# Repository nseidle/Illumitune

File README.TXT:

Illumitune is a exhibit at a kid's museum that has 8 infrared channels. When a channel is broken, a light turns on and a tone is played.

More information can be found at: http://www.sparkfun.com/tutorials/282

This repository contains all the firmware and design files for the various parts of the electronics. It also contains the logs from various dates. These logs show the usage information and are used for debugging and use trends.

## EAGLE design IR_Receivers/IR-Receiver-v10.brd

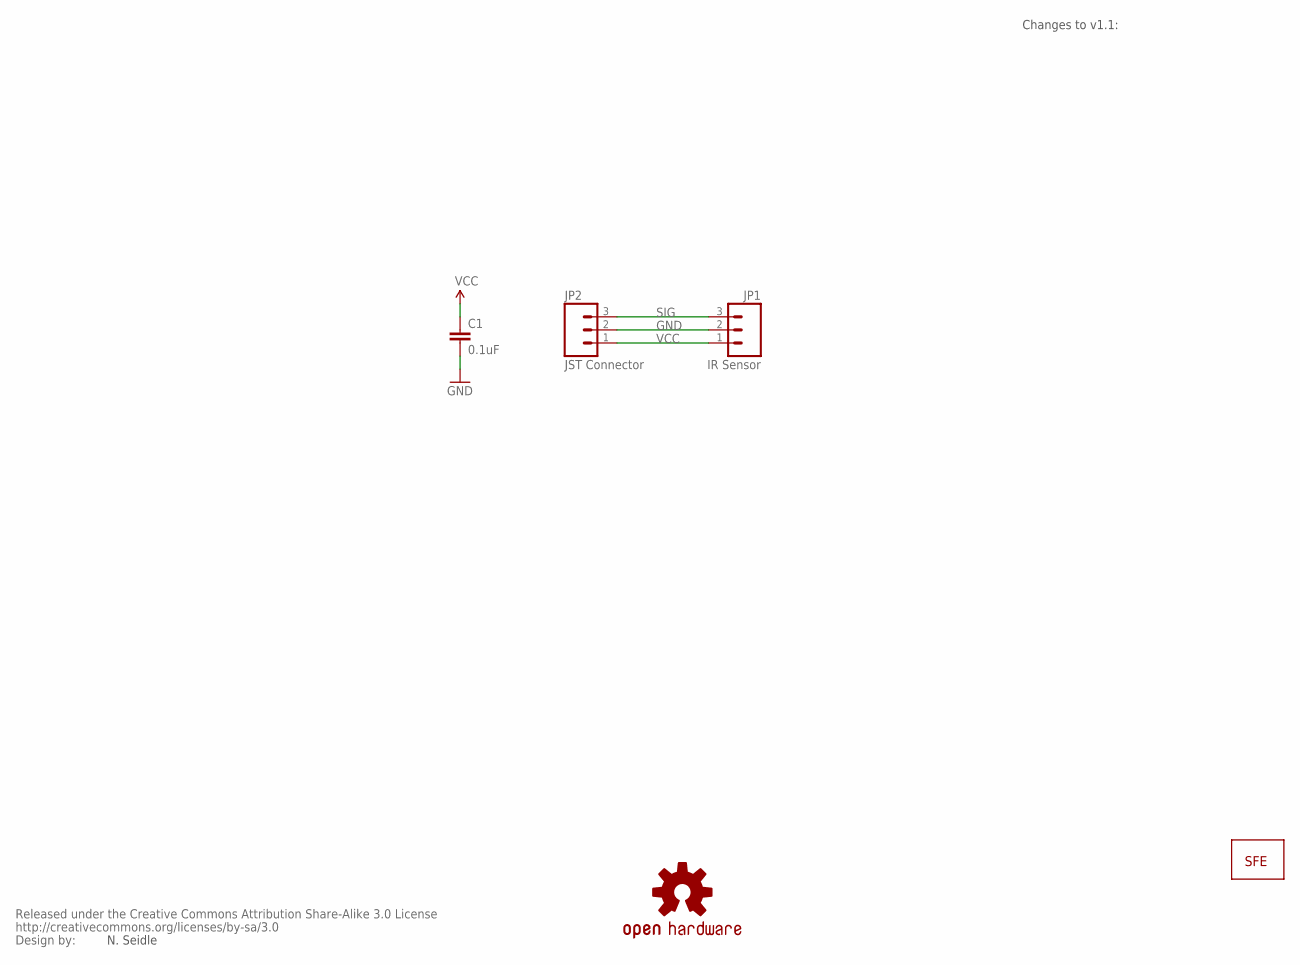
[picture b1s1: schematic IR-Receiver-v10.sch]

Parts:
C1: 0.1uF; CAP-PTH-SMALL2
JP1: IR Sensor; 1X03
JP2: JST Connector; JST-3-PTH
U$1: LOGO-SFESK; SFE-LOGO-FLAME
U$2: CREATIVE_COMMONS
U$4: OSHW-LOGOS; OSHW-LOGO-S

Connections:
GND: C1.2, JP1.2, JP2.2
SIG: JP1.3, JP2.3
VCC: C1.1, JP1.1, JP2.1

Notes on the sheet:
N. Seidle
Changes to v1.1:

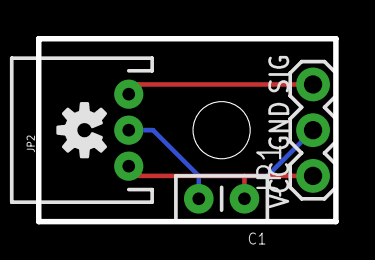
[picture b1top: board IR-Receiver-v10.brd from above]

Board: 2 copper layers, 16.5 x 10.2 mm, 6 parts (1 on the bottom side), 3 nets.

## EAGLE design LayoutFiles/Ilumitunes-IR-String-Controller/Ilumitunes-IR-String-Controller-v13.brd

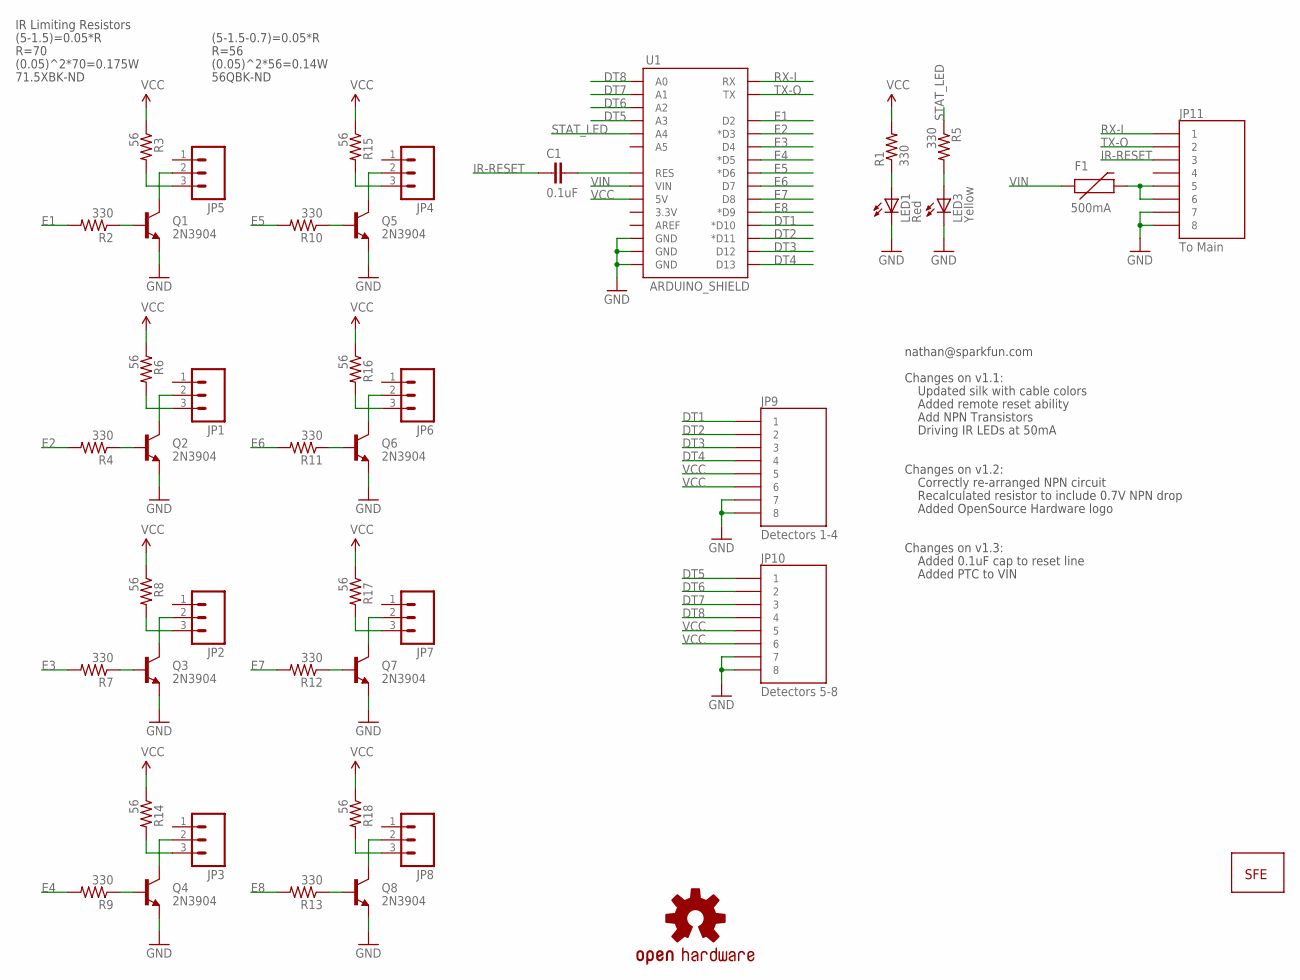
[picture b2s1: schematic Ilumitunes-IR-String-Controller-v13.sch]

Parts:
C1: 0.1uF; CAP-PTH-SMALL2
F1: 500mA; PTC
JP1, JP2, JP3, JP4, JP5, JP6, JP7, JP8: M03JST-PTH-VERT; JST-3-PTH-VERT
JP9: Detectors 1-4; RJ45-8
JP10: Detectors 5-8; RJ45-8
JP11: To Main; RJ45-8
LED1: Red; LED5MM
LED3: Yellow; LED5MM
Q1, Q2, Q3, Q4, Q5, Q6, Q7, Q8: 2N3904; TO-92
R1, R2, R4, R5, R7, R9, R10, R11, R12, R13: 330; AXIAL-0.3
R3, R6, R8, R14, R15, R16, R17, R18: 56; AXIAL-0.3
U1: ARDUINO_SHIELD; DUEMILANOVE_SHIELD_NOHOLES
U$1: LOGO-SFENEW; SFE-NEW-WEBLOGO
U$3: OSHW-LOGOS; OSHW-LOGO-S

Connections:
DT1: JP9.1, U1.D10 (*D10)
DT2: JP9.2, U1.D11 (*D11)
DT3: JP9.3, U1.D12
DT4: JP9.4, U1.D13
DT5: JP10.1, U1.A3
DT6: JP10.2, U1.A2
DT7: JP10.3, U1.A1
DT8: JP10.4, U1.A0
E1: R2.P$2 (2), U1.D2
E2: R4.P$2 (2), U1.D3 (*D3)
E3: R7.P$2 (2), U1.D4
E4: R9.P$2 (2), U1.D5 (*D5)
E5: R10.P$2 (2), U1.D6 (*D6)
E6: R11.P$2 (2), U1.D7
E7: R12.P$2 (2), U1.D8
E8: R13.P$2 (2), U1.D9 (*D9)
GND: JP9.7, JP9.8, JP10.7, JP10.8, JP11.7, JP11.8, LED1.K (C), LED3.K (C), Q1.1 (E), Q2.1 (E), Q3.1 (E), Q4.1 (E), Q5.1 (E), Q6.1 (E), Q7.1 (E), Q8.1 (E), U1.GND@0 (GND), U1.GND@1 (GND), U1.GND@2 (GND)
IR-RESET: C1.1, JP11.3
unnamed: LED1.A, R1.P$1 (1)
unnamed: Q1.2 (B), R2.P$1 (1)
unnamed: JP5.2, Q1.3 (C)
unnamed: LED3.A, R5.P$2 (2)
unnamed: JP5.3, R3.P$2 (2)
unnamed: JP1.2, Q2.3 (C)
unnamed: JP3.2, Q4.3 (C)
unnamed: JP8.2, Q8.3 (C)
unnamed: Q2.2 (B), R4.P$1 (1)
unnamed: JP1.3, R6.P$2 (2)
unnamed: Q3.2 (B), R7.P$1 (1)
unnamed: Q4.2 (B), R9.P$1 (1)
unnamed: Q6.2 (B), R11.P$1 (1)
unnamed: JP4.2, Q5.3 (C)
unnamed: JP6.3, R16.P$2 (2)
unnamed: Q7.2 (B), R12.P$1 (1)
unnamed: JP2.3, R8.P$2 (2)
unnamed: JP3.3, R14.P$2 (2)
unnamed: Q5.2 (B), R10.P$1 (1)
unnamed: C1.2, U1.RES
unnamed: JP4.3, R15.P$2 (2)
unnamed: JP6.2, Q6.3 (C)
unnamed: JP7.3, R17.P$2 (2)
unnamed: Q8.2 (B), R13.P$1 (1)
unnamed: JP7.2, Q7.3 (C)
unnamed: JP8.3, R18.P$2 (2)
unnamed: JP2.2, Q3.3 (C)
unnamed: F1.P$2 (2), JP11.5, JP11.6
RX-I: JP11.1, U1.RX
STAT_LED: R5.P$1 (1), U1.A4
TX-O: JP11.2, U1.TX
VCC: JP9.5, JP9.6, JP10.5, JP10.6, R1.P$2 (2), R3.P$1 (1), R6.P$1 (1), R8.P$1 (1), R14.P$1 (1), R15.P$1 (1), R16.P$1 (1), R17.P$1 (1), R18.P$1 (1), U1.5V
VIN: F1.P$1 (1), U1.VIN

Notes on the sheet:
Changes on v1.1:
Updated silk with cable colors
Added remote reset ability
nathan@sparkfun.com
Add NPN Transistors
(5-1.5)=0.05*R
R=70
(0.05)^2*70=0.175W
71.5XBK-ND
Driving IR LEDs at 50mA
IR Limiting Resistors
(5-1.5-0.7)=0.05*R
R=56
(0.05)^2*56=0.14W
56QBK-ND
Changes on v1.2:
Correctly re-arranged NPN circuit
Recalculated resistor to include 0.7V NPN drop
Added OpenSource Hardware logo
Changes on v1.3:
Added 0.1uF cap to reset line
Added PTC to VIN

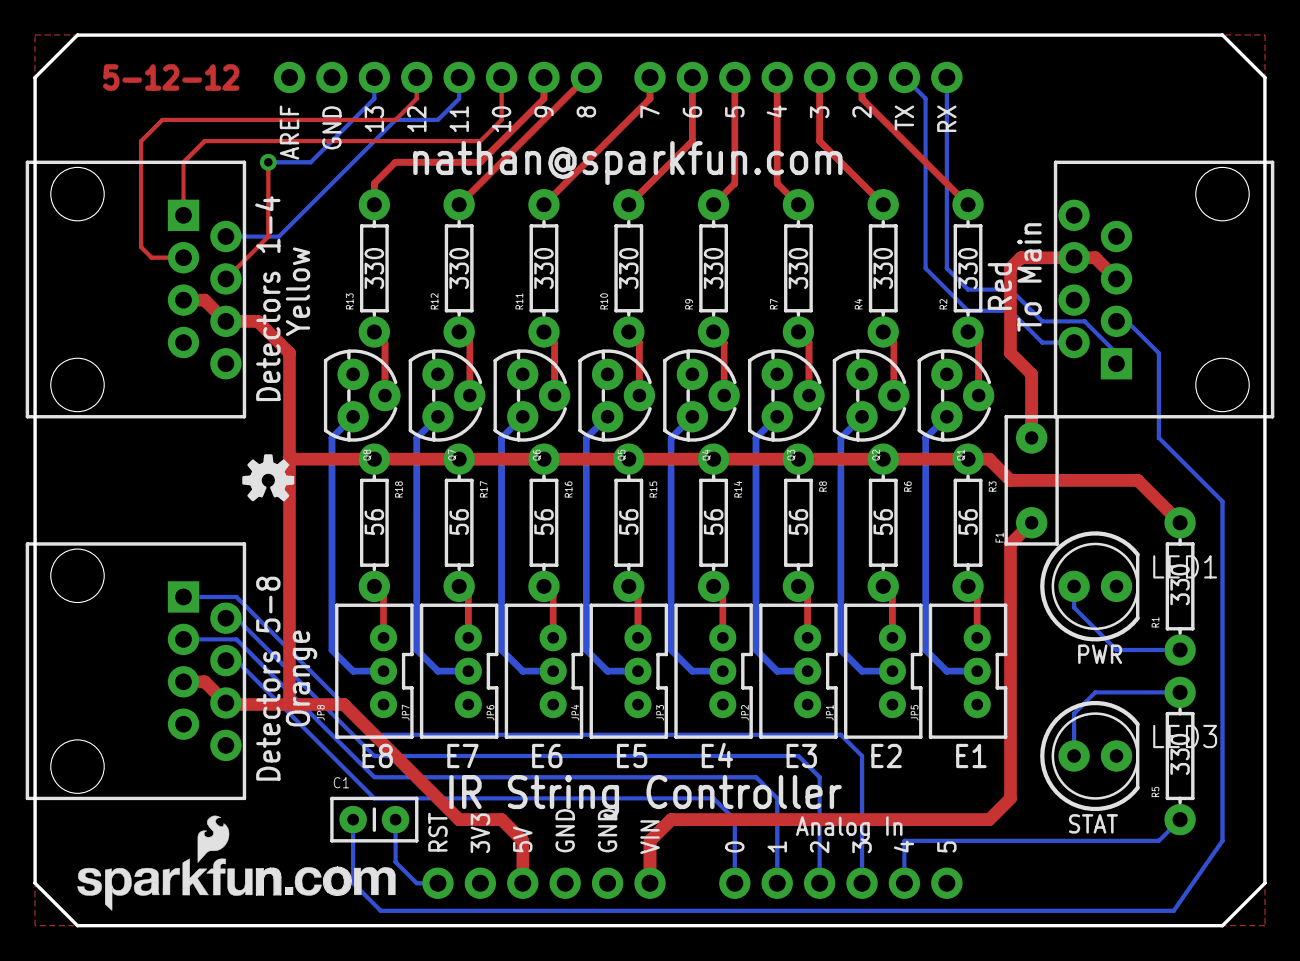
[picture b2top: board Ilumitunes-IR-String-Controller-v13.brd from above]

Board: 2 copper layers, 73.7 x 53.3 mm, 44 parts (0 on the bottom side), 51 nets.

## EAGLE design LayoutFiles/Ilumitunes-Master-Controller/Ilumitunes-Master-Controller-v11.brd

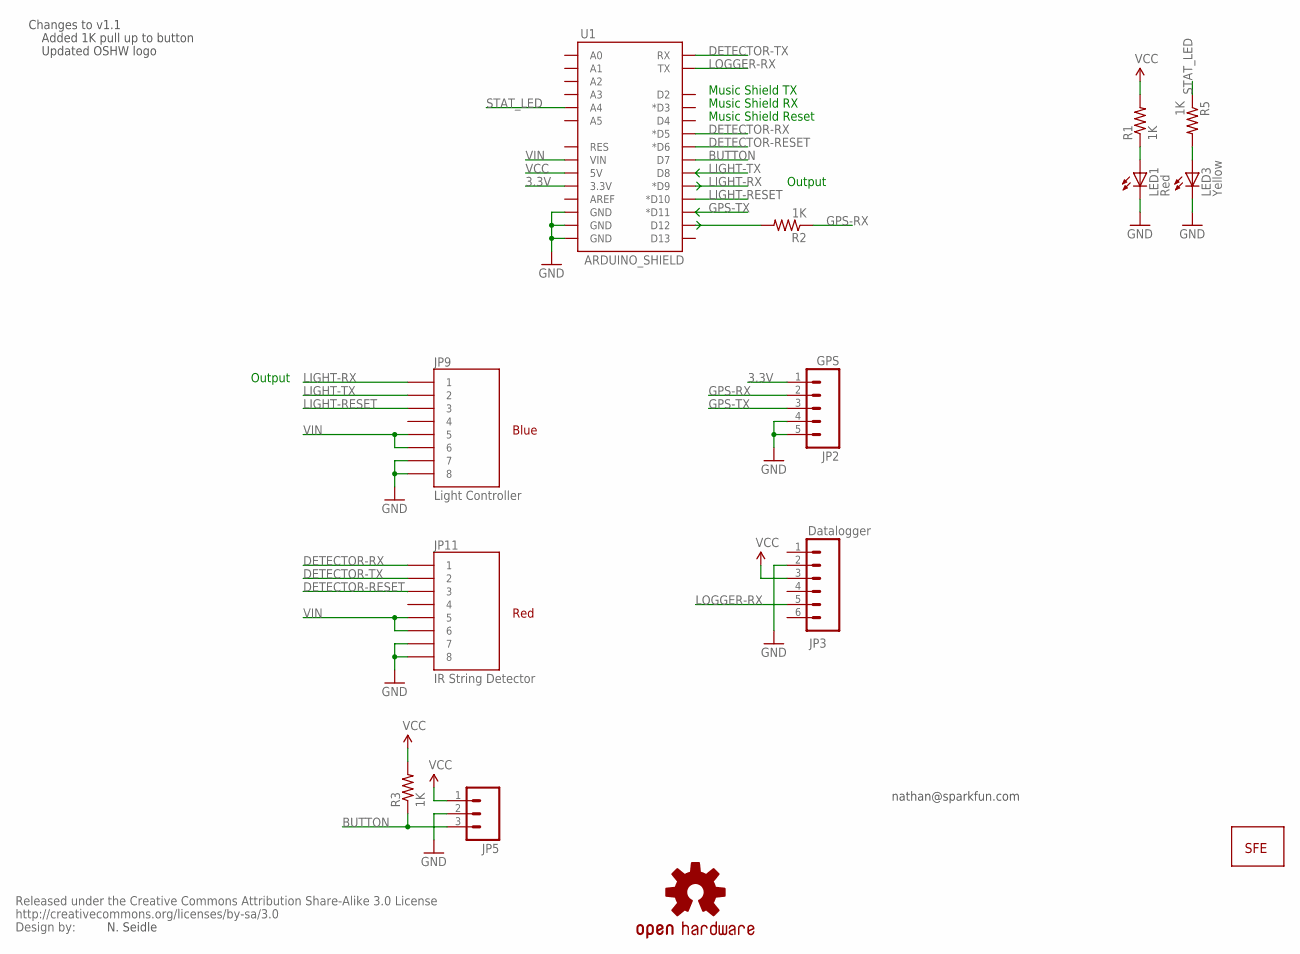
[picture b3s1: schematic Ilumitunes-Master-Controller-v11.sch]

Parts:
JP2: GPS; 1X05
JP3: Datalogger; 1X06
JP5: M03JST-PTH-VERT; JST-3-PTH-VERT
JP9: Light Controller; RJ45-8
JP11: IR String Detector; RJ45-8
LED1: Red; LED5MM
LED3: Yellow; LED5MM
R1, R2, R3, R5: 1K; AXIAL-0.3
U1: ARDUINO_SHIELD; DUEMILANOVE_SHIELD
U$1: LOGO-SFENEW; SFE-NEW-WEBLOGO
U$2: CREATIVE_COMMONS
U$3: OSHW-LOGOS; OSHW-LOGO-S

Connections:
3.3V: JP2.1, U1.3.3V
BUTTON: JP5.3, R3.P$1 (1), U1.D7
DETECTOR-RESET: JP11.3, U1.D6 (*D6)
DETECTOR-RX: JP11.1, U1.D5 (*D5)
DETECTOR-TX: JP11.2, U1.RX
GND: JP2.4, JP2.5, JP3.2, JP5.2, JP9.7, JP9.8, JP11.7, JP11.8, LED1.K (C), LED3.K (C), U1.GND@0 (GND), U1.GND@1 (GND), U1.GND@2 (GND)
GPS-RX: JP2.2, R2.P$1 (1)
GPS-TX: JP2.3, U1.D11 (*D11)
LIGHT-RESET: JP9.3, U1.D10 (*D10)
LIGHT-RX: JP9.1, U1.D9 (*D9)
LIGHT-TX: JP9.2, U1.D8
LOGGER-RX: JP3.5, U1.TX
unnamed: LED1.A, R1.P$1 (1)
unnamed: R2.P$2 (2), U1.D12
unnamed: LED3.A, R5.P$2 (2)
STAT_LED: R5.P$1 (1), U1.A4
VCC: JP3.3, JP5.1, R1.P$2 (2), R3.P$2 (2), U1.5V
VIN: JP9.5, JP9.6, JP11.5, JP11.6, U1.VIN

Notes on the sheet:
Music Shield RX
Music Shield Reset
Music Shield TX
Blue
Red
Output
nathan@sparkfun.com
Changes to v1.1
N. Seidle
Added 1K pull up to button
Updated OSHW logo

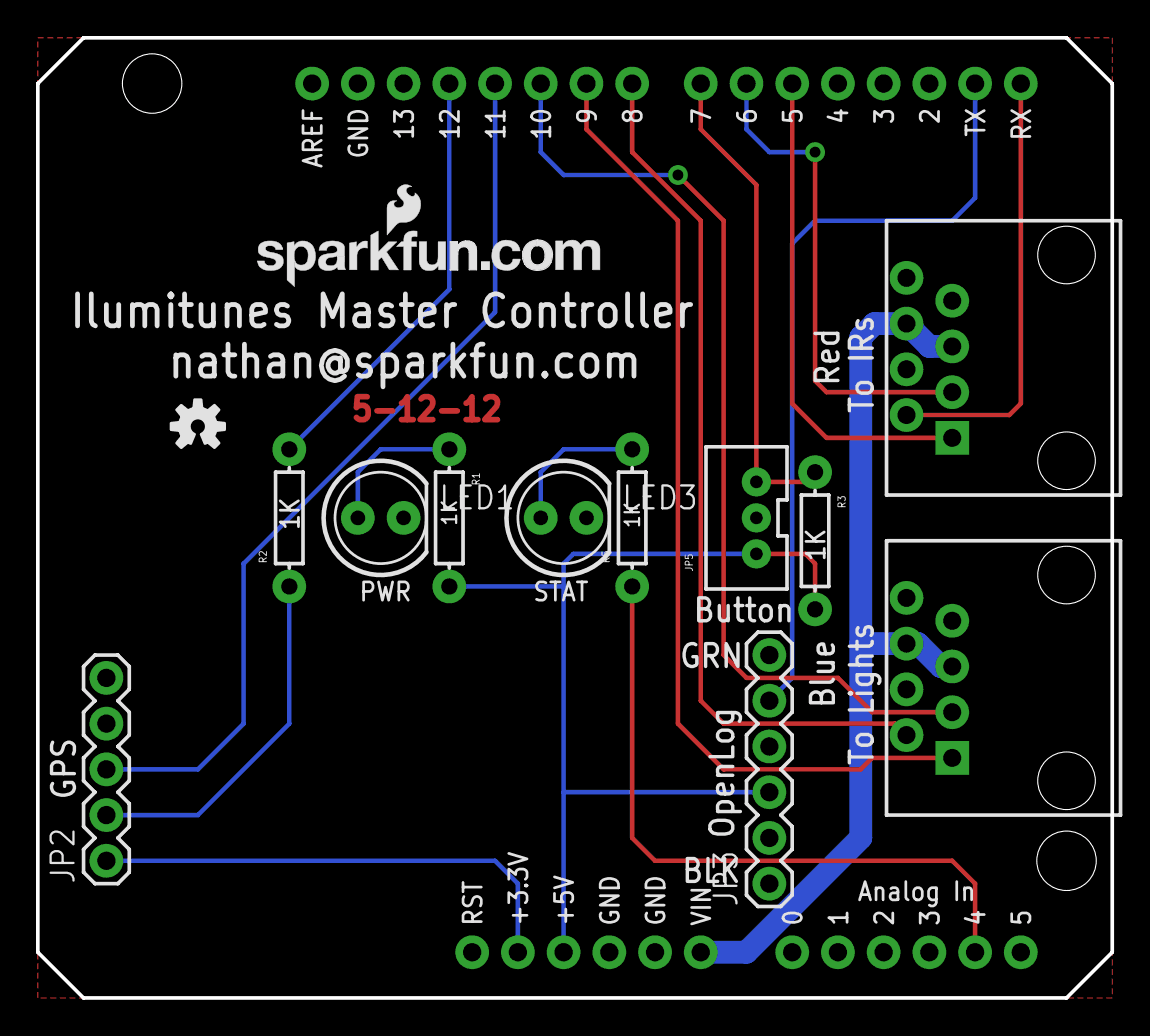
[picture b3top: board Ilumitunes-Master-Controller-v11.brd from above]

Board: 2 copper layers, 59.7 x 53.3 mm, 15 parts (0 on the bottom side), 18 nets.

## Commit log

2012-04-25 First commit.
2012-04-25 Adding Eagle layout files
2012-04-25 Removed IR support from Master controller. Log all error ridden data. Check for errors from light controller.
    Added ToDo for PTCs on Master Controller.
2012-05-13 Added more PTC and decoupling to string controller at breakout.
2012-07-04 Updated IR controller to work with Arduino v1.0
    Not yet tested. Unsure if Av1.0 does anything weird with the microsecond
    delays or inline assembly.
2012-07-04 Updates logs. Added pull up to button on master. Added PTC and reset cap to IR controller.
2012-07-04 Testing out the merge branch tool on new github windows.
2012-07-15 Added a reset routine every 4 hours. Updated logs.
2012-10-21 Illumitune is now stable. Updating logs.
    Illumitune has been stably running for a few months now. I believe the
    reset every four hours was the main fix. This was not possible before
    changing out the amp for a simple, solid-state, low cost solution
    ($20!). I hope you can learn something from all these trials and
    tribulations.
    From now on there will probably only be log updates as the code is
2013-01-14 Added small breakout for IR receiver. Updated logs.
    Added a small breakout board for the IR receiver. This board has a
    mounting hole and a JST connector to make swapping IR receivers in/out a
    little easier.
2013-04-08 Adding latest logs.

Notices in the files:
parts and their libraries:
SparkFun: Released under the Creative Commons Attribution Share-Alike 3.0 License
SparkFun: http://creativecommons.org/licenses/by-sa/3.0
SparkFun-Connectors: Licensing: CC v3.0 Share-Alike You are welcome to use this library for commercial purposes.
